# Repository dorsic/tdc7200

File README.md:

# tdc7200
Thinkering with TI TDC7200 chip, reading and connecting to Raspberry PI (RPi).

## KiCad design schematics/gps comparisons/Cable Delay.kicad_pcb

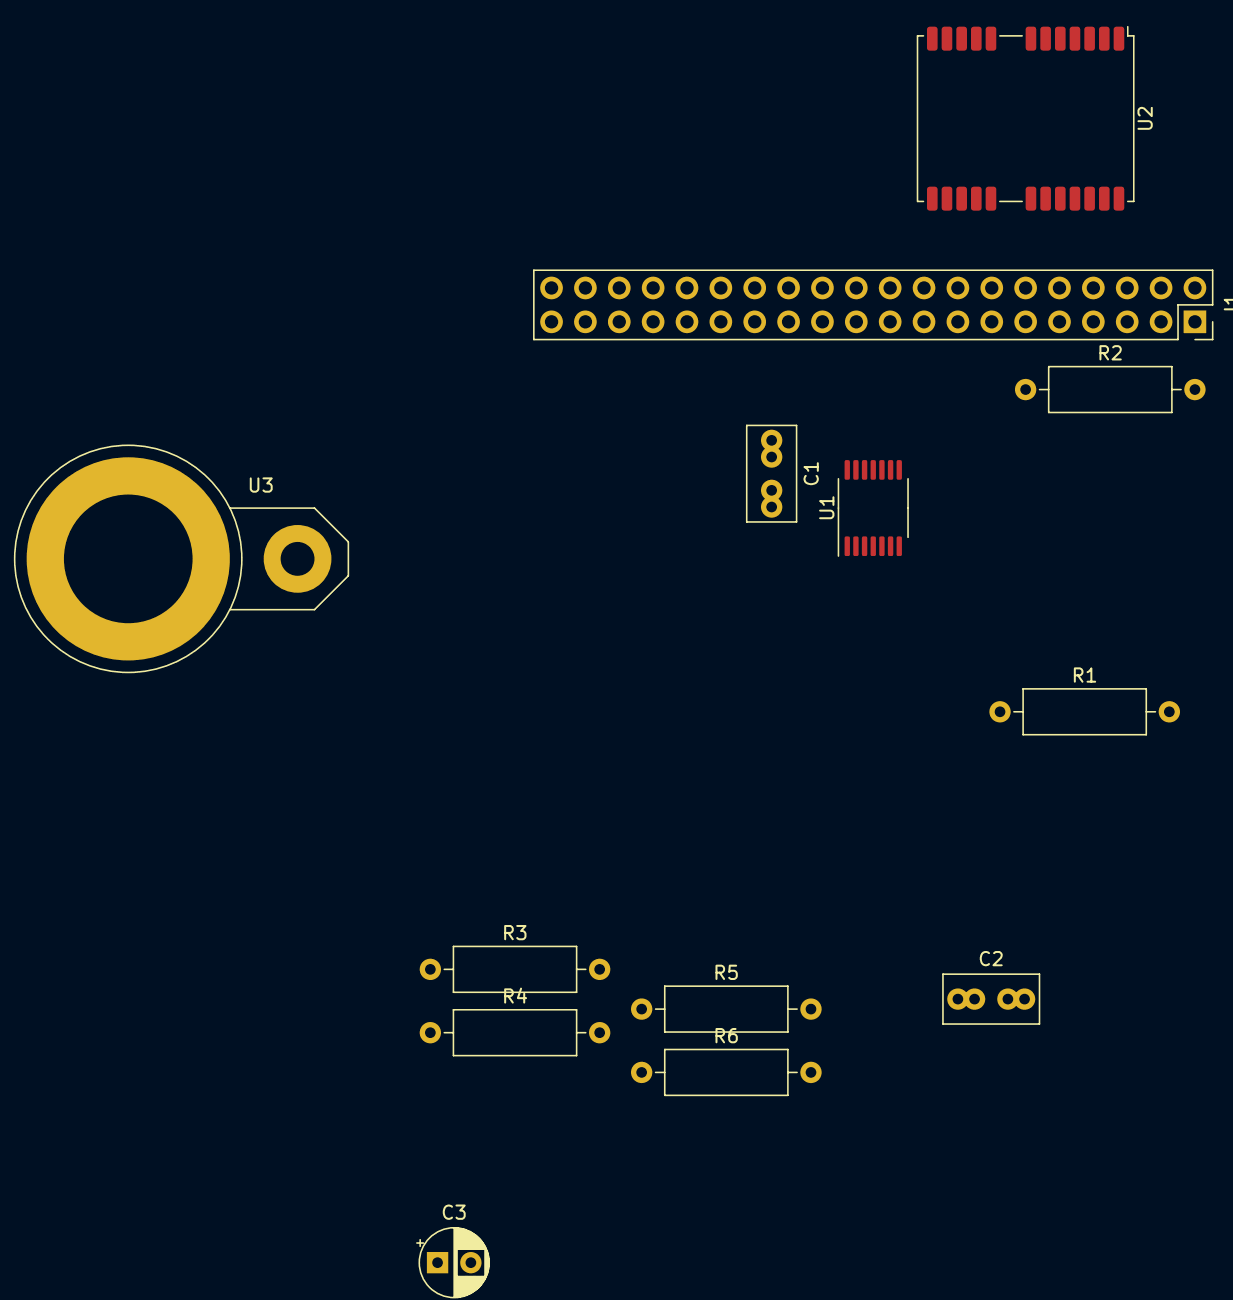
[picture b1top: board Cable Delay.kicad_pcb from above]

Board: 2 copper layers, 13 parts (0 on the bottom side), 18 nets, no tracks yet.

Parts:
C1: 104; C_Rect_L7.0mm_W3.5mm_P2.50mm_P5.00mm
C2: 105; C_Rect_L7.0mm_W3.5mm_P2.50mm_P5.00mm
C3: 1uF; CP_Radial_D5.0mm_P2.50mm
J1: Raspberry_Pi_2_3; PinSocket_2x20_P2.54mm_Vertical
R1: 1k; R_Axial_DIN0309_L9.0mm_D3.2mm_P12.70mm_Horizontal
R2: 10k; R_Axial_DIN0309_L9.0mm_D3.2mm_P12.70mm_Horizontal
R3, R4, R5, R6: 100; R_Axial_DIN0309_L9.0mm_D3.2mm_P12.70mm_Horizontal
U1: TDC7200; TSSOP-14_4.4x5mm_P0.65mm
U2: NEO-M8N; ublox_NEO
U3: CAM-M8N; BNC_PanelMountable_Vertical

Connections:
Earth: C1.2, C2.2, C3.2, U1.7, U2.10, U2.12, U2.13, U2.24
unnamed: C1.1, U1.14, U2.23
unnamed: C2.1, U1.13
unnamed: C3.1, J1.1, R2.2
unnamed: J1.8, U2.21
unnamed: J1.10, U2.20
unnamed: J1.12, R1.2
unnamed: J1.19, U1.9
unnamed: J1.21, U1.10
unnamed: J1.23, U1.12
unnamed: J1.24, U1.11
unnamed: J1.38, R2.1, U1.8
unnamed: J1.40, U1.2
unnamed: R1.1, U1.1
unnamed: R3.1, R4.1, U1.3
unnamed: R3.2, R4.2, U2.3
unnamed: R5.1, R6.1, U1.4
unnamed: R5.2, R6.2, U1.5

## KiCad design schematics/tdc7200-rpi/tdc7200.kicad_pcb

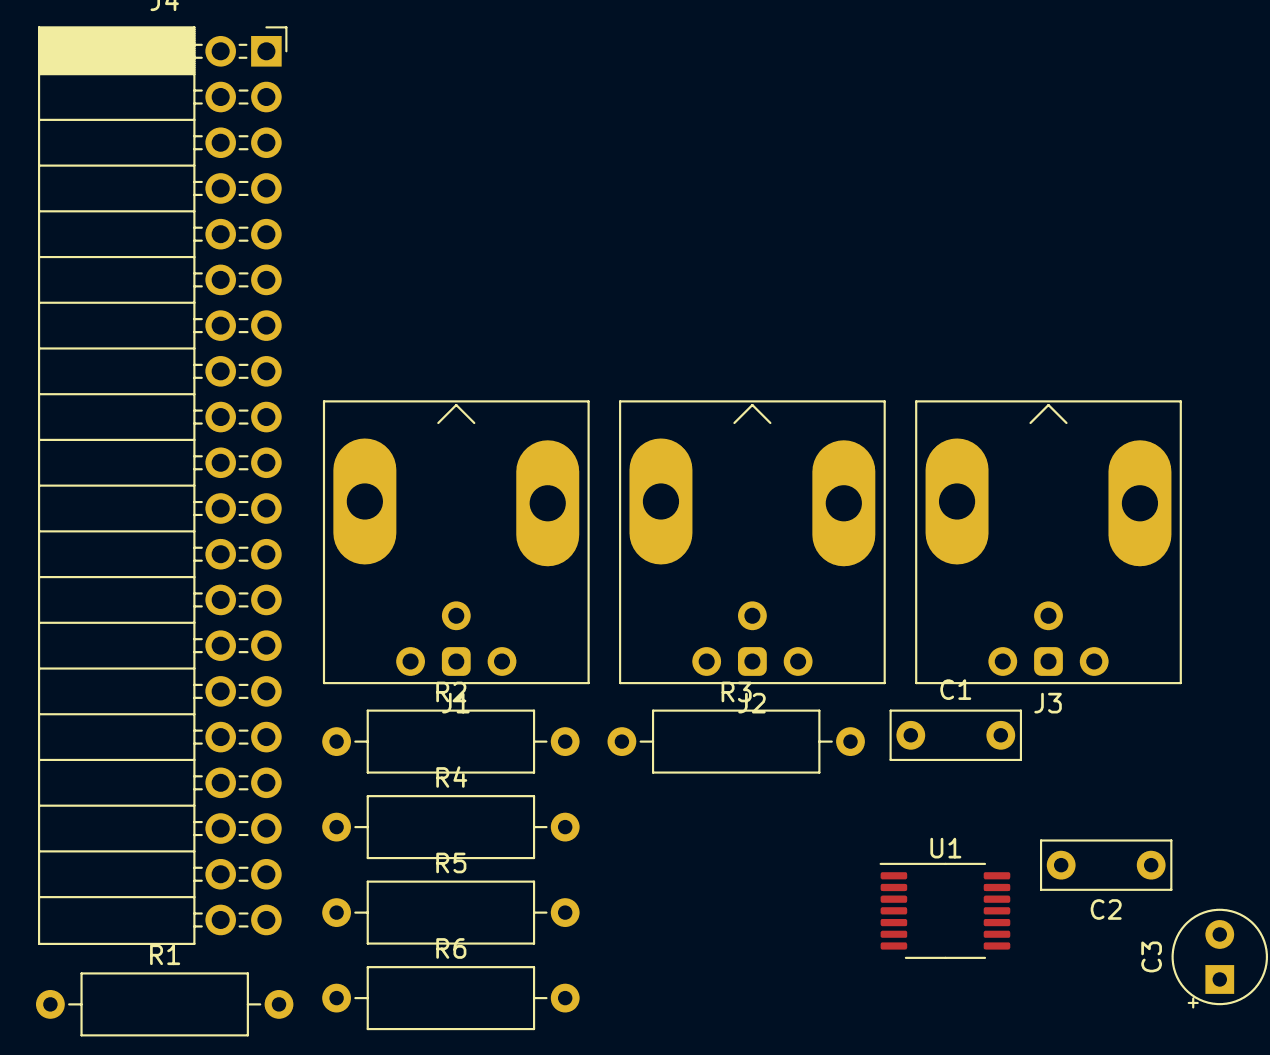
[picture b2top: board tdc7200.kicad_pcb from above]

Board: 2 copper layers, 14 parts (0 on the bottom side), 16 nets, no tracks yet.

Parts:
C1: 105; C_Rect_L7.0mm_W2.5mm_P5.00mm
C2: 104; C_Rect_L7.0mm_W2.5mm_P5.00mm
C3: 1,0+uF; CP_Radial_Tantal_D5.0mm_P2.50mm
J1: START; BNC_Amphenol_031-6575_Horizontal
J2: STOP; BNC_Amphenol_031-6575_Horizontal
J3: 1-16MHz Clock; BNC_Amphenol_031-6575_Horizontal
J4: Raspberry_Pi_2-4; PinSocket_2x20_P2.54mm_Horizontal
R1, R2: 50; R_Axial_DIN0309_L9.0mm_D3.2mm_P12.70mm_Horizontal
R3, R4: 100; R_Axial_DIN0309_L9.0mm_D3.2mm_P12.70mm_Horizontal
R5: 1k; R_Axial_DIN0309_L9.0mm_D3.2mm_P12.70mm_Horizontal
R6: 10k; R_Axial_DIN0309_L9.0mm_D3.2mm_P12.70mm_Horizontal
U1: TDC7200; TSSOP-14_4.4x5mm_P0.65mm

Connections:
Earth: C1.1, C2.1, C3.2, J1.2, J2.2, J3.2, J4.39, R3.1, U1.7
unnamed: C1.2, U1.13
unnamed: C2.2, C3.1, J4.1, R4.2, R6.2, U1.14
unnamed: J1.1, J4.29, R1.2, R3.2, R4.1
unnamed: J2.1, R2.2
unnamed: J3.1, U1.5
unnamed: J4.12, R5.2
unnamed: J4.19, U1.9
unnamed: J4.21, U1.10
unnamed: J4.23, U1.12
unnamed: J4.24, U1.11
unnamed: J4.38, R6.1, U1.8
unnamed: J4.40, U1.2
unnamed: R1.1, U1.3
unnamed: R2.1, U1.4
unnamed: R5.1, U1.1

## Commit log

2023-10-10 support for daily log files
